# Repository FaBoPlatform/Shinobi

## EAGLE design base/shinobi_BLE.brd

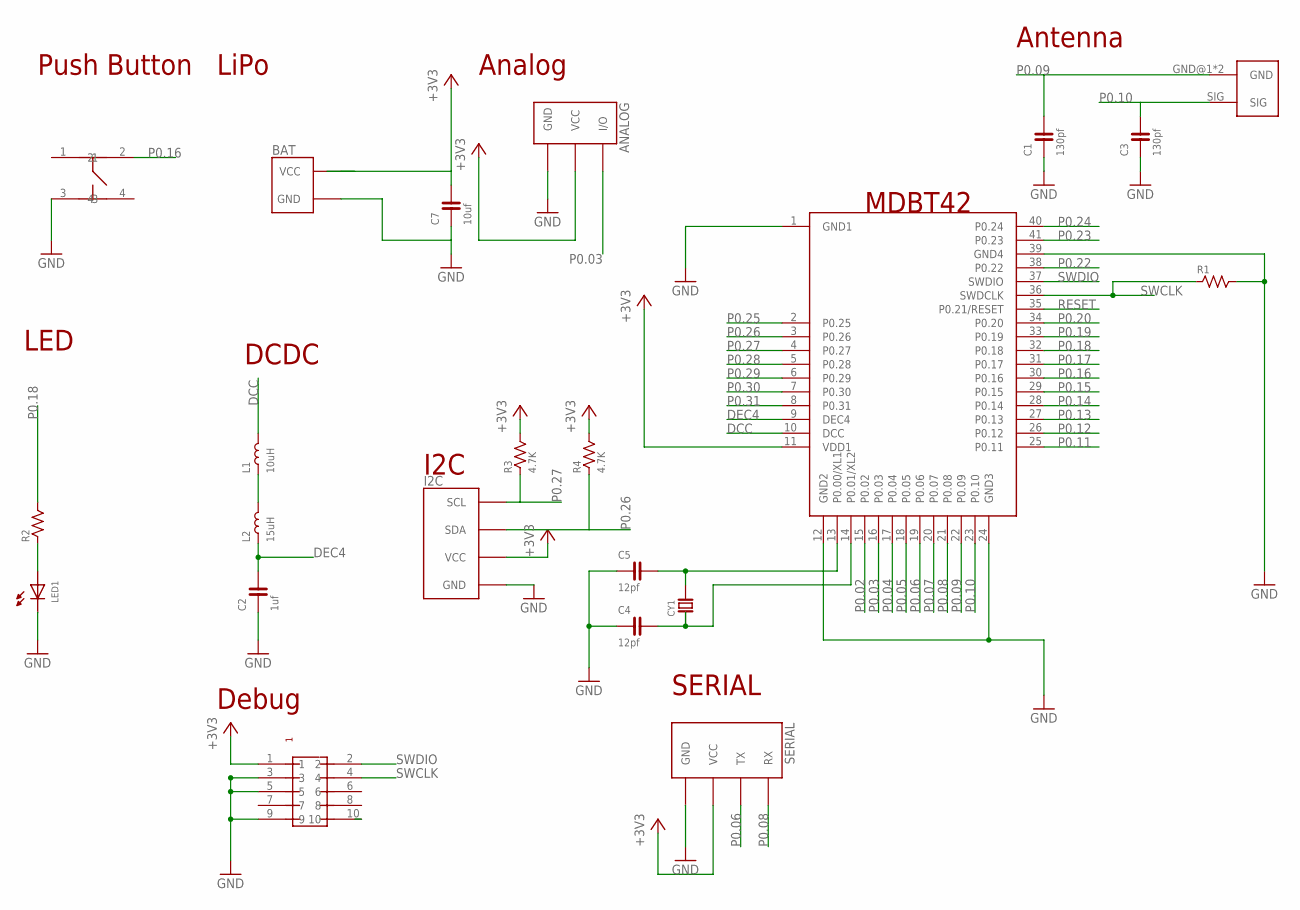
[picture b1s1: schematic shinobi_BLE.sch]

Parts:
ANALOG: FABO_BRICK_3PIN-S03B-PASK-2_LONG; FABO_BRICK_3PIN_S03B-PASK-2_LONG
BAT: FABO_BRICK_2PIN_SIDE; FABO_BRICK_2PIN_S02B−PASK-2_SILK
C1, C3: 130pf; 0603
C2: 1uf; 0603
C4, C5: 12pf; 0603
C7: 10uf; 0603
CY1: CRYSTAL-ABS07; ABRACON-ABS07-32.768KHZ
I2C: FABO_BRICK_I2C-S04B-PASK-2_LONG; FABO_BRICK_I2C_S04B-PASK-2_LONG
L1: 10uH; 0603
L2: 15uH; 1812
LED1: LED-0603; 0603
R1, R2: RESISTOR-0603; 0603
R3, R4: 4.7K; 0603
SERIAL: FABO_BRICK_SERIAL-S04B-PASK-2_LONG; FABO_BRICK_SERIAL_S04B-PASK-2_LONG
U$2: RAYTAC-MDBT42
U$4: PIN-HEADER-SMT(1.27MM)2X5
U$5: SWICTH-4P(KMR2); SWITCH-4P(KMR2)
UF1: HIROSE-U.FL; HIROSE-UF.L

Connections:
+3V3: ANALOG.VCC, BAT.VCC, C7.2, I2C.VCC, R3.2, R4.2, SERIAL.VCC, U$2.11 (VDD1), U$4.1
DCC: L1.2, U$2.10 (DCC)
DEC4: C2.2, L2.P$1 (1), U$2.9 (DEC4)
GND: ANALOG.GND, BAT.GND, C1.1, C2.1, C3.1, C4.1, C5.1, C7.1, I2C.GND, LED1.CATHODE, R1.2, SERIAL.GND, U$2.1 (GND1), U$2.12 (GND2), U$2.24 (GND3), U$2.39 (GND4), U$4.3, U$4.5, U$4.9, U$5.3
unnamed: LED1.ANODE, R2.1
unnamed: L1.1, L2.P$2 (2)
unnamed: C5.2, CY1.P$2, U$2.13 (P0.00/XL1)
unnamed: C4.2, CY1.P$1, U$2.14 (P0.01/XL2)
P0.02: U$2.15 (P0.02)
P0.03: ANALOG.I/O, U$2.16 (P0.03)
P0.04: U$2.17 (P0.04)
P0.05: U$2.18 (P0.05)
P0.06: SERIAL.TX, U$2.19 (P0.06)
P0.07: U$2.20 (P0.07)
P0.08: SERIAL.RX, U$2.21 (P0.08)
P0.09: C1.2, U$2.22 (P0.09), UF1.GND@1 (GND), UF1.GND@2 (GND)
P0.10: C3.2, U$2.23 (P0.10), UF1.SIG
P0.11: U$2.25 (P0.11)
P0.12: U$2.26 (P0.12)
P0.13: U$2.27 (P0.13)
P0.14: U$2.28 (P0.14)
P0.15: U$2.29 (P0.15)
P0.16: U$2.30 (P0.16), U$5.2
P0.17: U$2.31 (P0.17)
P0.18: R2.2, U$2.32 (P0.18)
P0.19: U$2.33 (P0.19)
P0.20: U$2.34 (P0.20)
P0.22: U$2.38 (P0.22)
P0.23: U$2.41 (P0.23)
P0.24: U$2.40 (P0.24)
P0.25: U$2.2 (P0.25)
P0.26: I2C.SDA, R4.1, U$2.3 (P0.26)
P0.27: I2C.SCL, R3.1, U$2.4 (P0.27)
P0.28: U$2.5 (P0.28)
P0.29: U$2.6 (P0.29)
P0.30: U$2.7 (P0.30)
P0.31: U$2.8 (P0.31)
RESET: U$2.35 (P0.21/RESET)
RESET1: U$4.10
SWCLK: R1.1, U$2.36 (SWDCLK), U$4.4
SWDIO: U$2.37 (SWDIO), U$4.2

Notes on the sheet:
Push Button
MDBT42
LED
Debug
DCDC
Analog
I2C
SERIAL
LiPo
Antenna

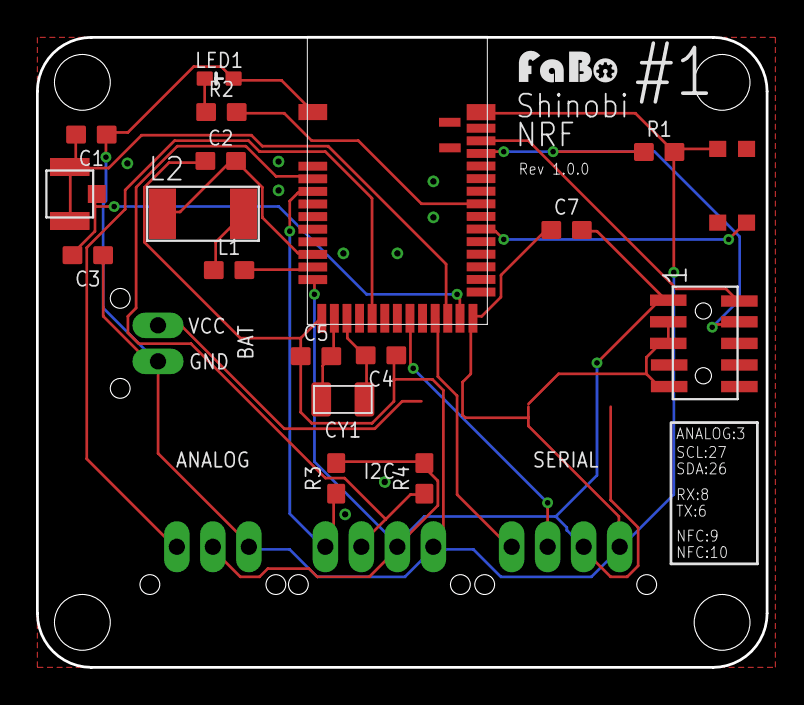
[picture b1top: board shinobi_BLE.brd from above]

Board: 2 copper layers, 40.5 x 35.0 mm, 24 parts (0 on the bottom side), 19 nets.

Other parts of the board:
U$1: FABO-SHINOBI
U$3: LOGO_FABO_S

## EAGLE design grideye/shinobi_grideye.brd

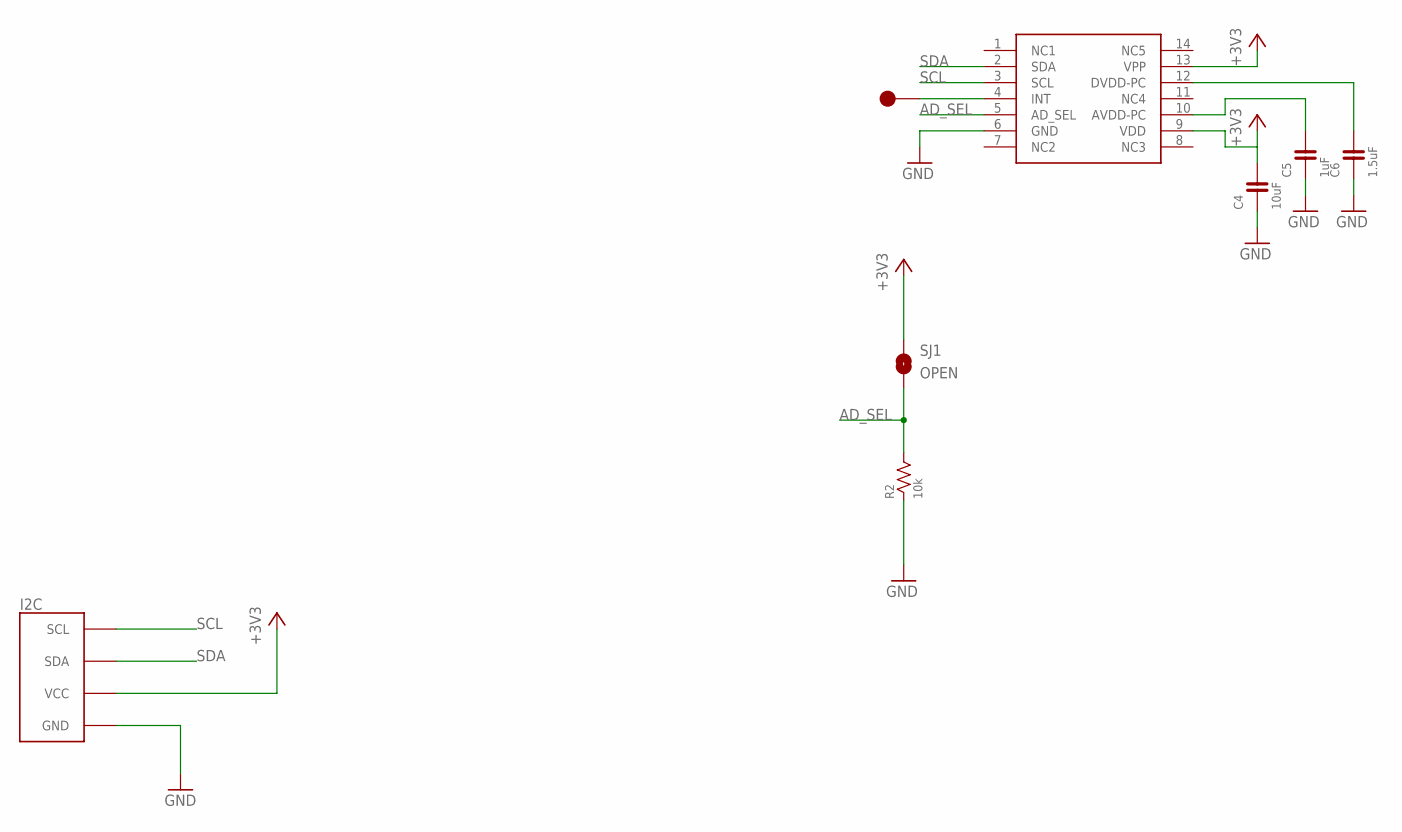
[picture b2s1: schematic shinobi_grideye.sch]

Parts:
C4: 10uF; 0603
C5: 1uF; 0603
C6: 1.5uF; 0603
GRIDEYE: PN-AMG8331; PANASONIC-AMG8831
I2C: FABO_BRICK_I2C-S04B-PASK-2_LONG; FABO_BRICK_I2C_S04B-PASK-2_LONG
INT: INT; TP-15
R2: 10k; 0603
SJ1: OPEN; SMD-JUMPER-2-OPEN

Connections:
+3V3: C4.2, GRIDEYE.9 (VDD), GRIDEYE.13 (VPP), I2C.VCC, SJ1.1
AD_SEL: GRIDEYE.5 (AD_SEL), R2.2, SJ1.2
GND: C4.1, C5.1, C6.1, GRIDEYE.6 (GND), I2C.GND, R2.1
unnamed: GRIDEYE.4 (INT), INT.1
unnamed: C6.2, GRIDEYE.12 (DVDD-PC)
unnamed: C5.2, GRIDEYE.10 (AVDD-PC)
SCL: GRIDEYE.3 (SCL), I2C.SCL
SDA: GRIDEYE.2 (SDA), I2C.SDA

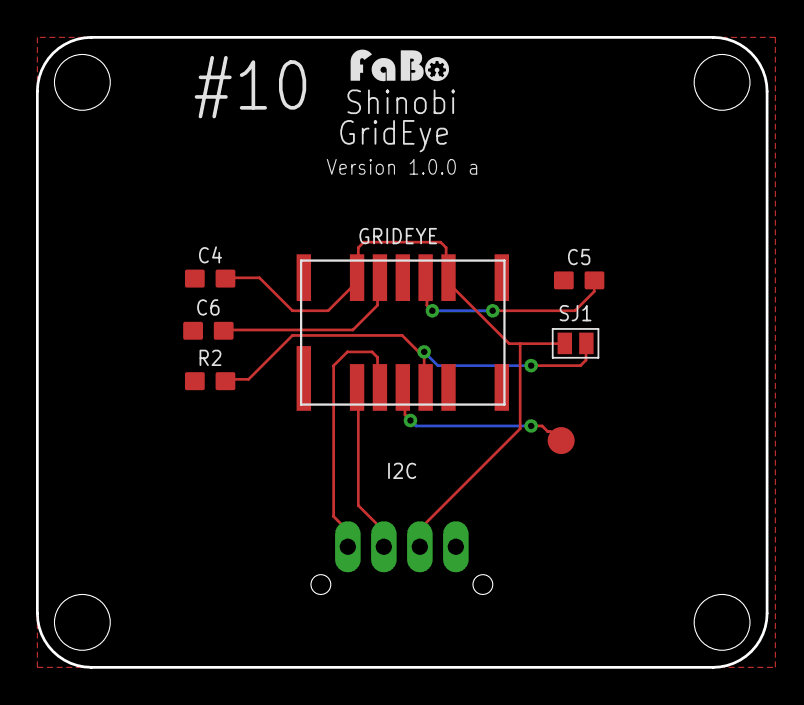
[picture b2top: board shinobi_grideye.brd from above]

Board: 2 copper layers, 40.5 x 35.0 mm, 10 parts (0 on the bottom side), 8 nets.

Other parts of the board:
U$2: LOGO_FABO_S
U$3: FABO-SHINOBI

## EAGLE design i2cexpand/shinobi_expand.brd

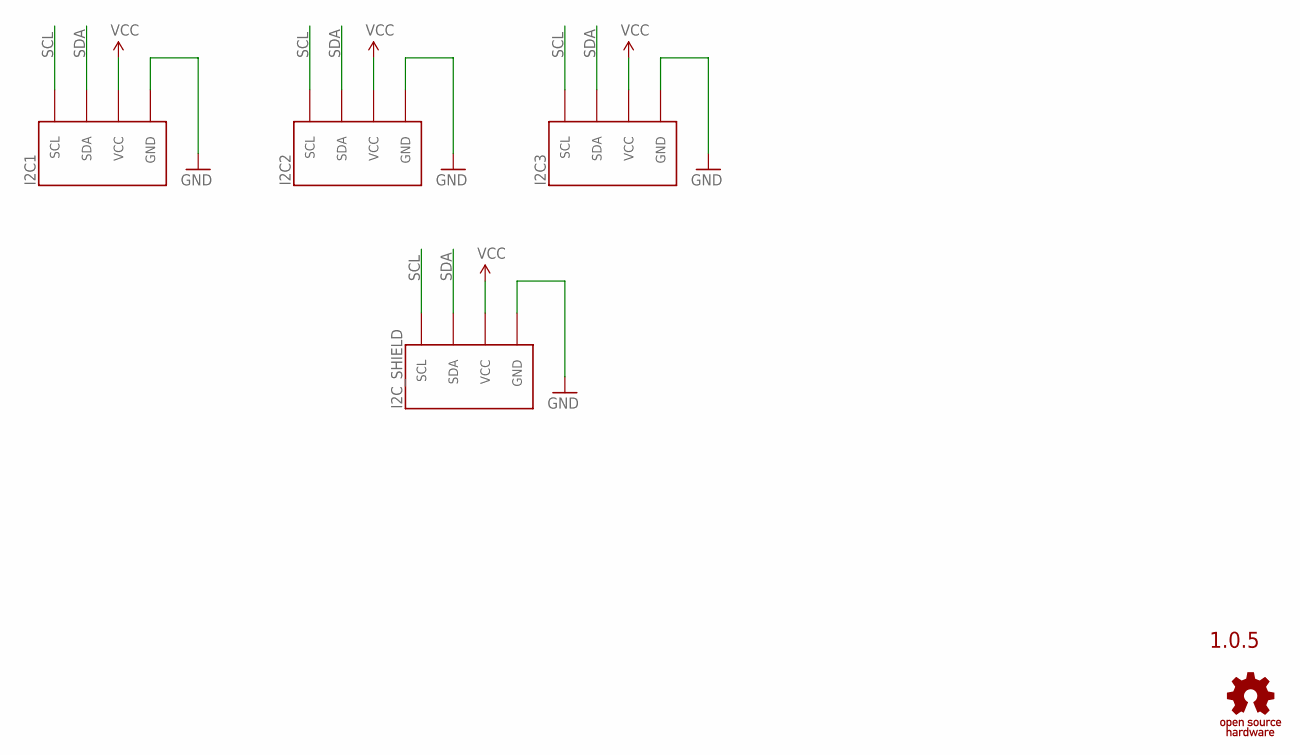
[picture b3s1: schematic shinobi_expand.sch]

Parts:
I2C1, I2C2, I2C3, I2C_SHIELD: FABO_BRICK_I2C-S04B-PASK-2_LONG; FABO_BRICK_I2C_S04B-PASK-2_LONG
U$11: LOGO_OSHW-M_BOTTOM; LOGO_OSHW_M_BOTTOM

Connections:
GND: I2C1.GND, I2C2.GND, I2C3.GND, I2C_SHIELD.GND
SCL: I2C1.SCL, I2C2.SCL, I2C3.SCL, I2C_SHIELD.SCL
SDA: I2C1.SDA, I2C2.SDA, I2C3.SDA, I2C_SHIELD.SDA
VCC: I2C1.VCC, I2C2.VCC, I2C3.VCC, I2C_SHIELD.VCC

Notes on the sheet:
1.0.5

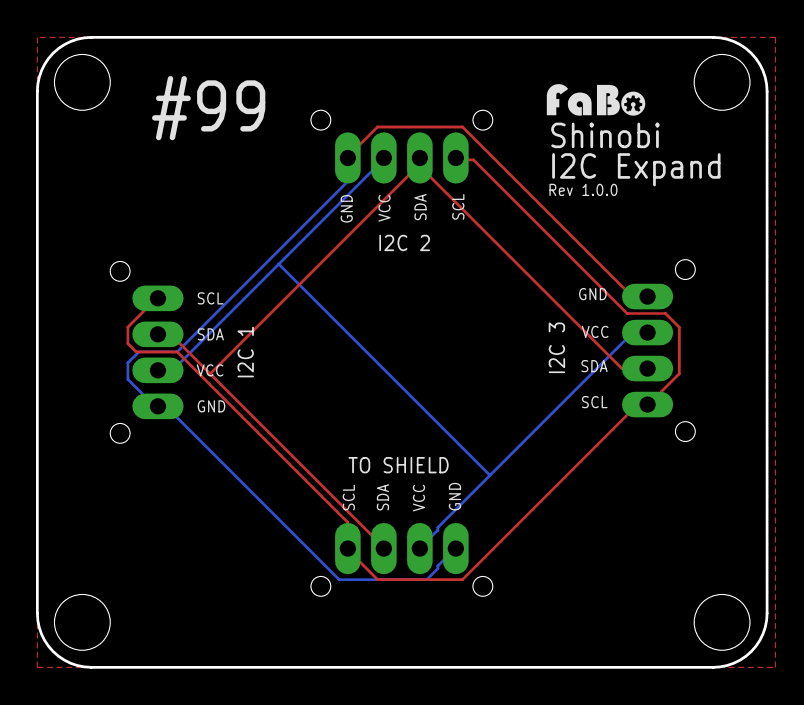
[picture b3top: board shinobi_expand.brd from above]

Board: 2 copper layers, 40.5 x 35.0 mm, 7 parts (0 on the bottom side), 4 nets.

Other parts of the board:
U$2: FABO-SHINOBI
U$3: LOGO_FABO_S

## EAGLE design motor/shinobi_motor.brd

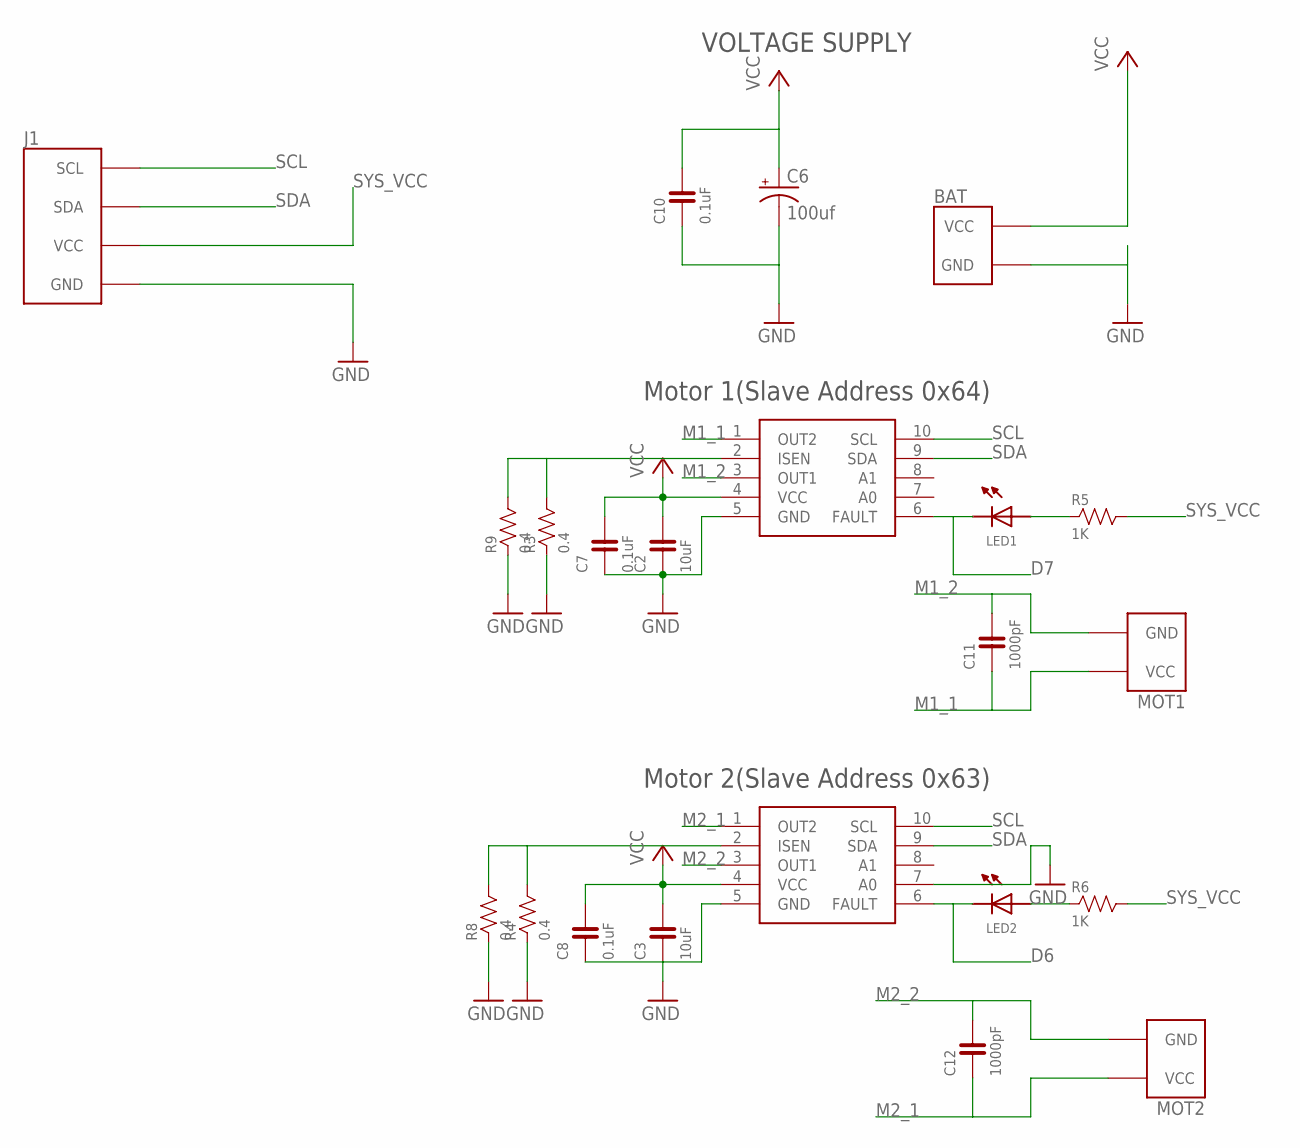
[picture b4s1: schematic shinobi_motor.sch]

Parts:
BAT: FABO_BRICK_2PIN_SIDE; FABO_BRICK_2PIN_S02B−PASK-2_SILK
C2, C3: 10uF; 0603
C6: 100uf; 153CLV-0405
C7, C8, C10: 0.1uF; 0603
C11, C12: 1000pF; 0603
J1: FABO_BRICK_I2C-S04B-PASK-2_LONG; FABO_BRICK_I2C_S04B-PASK-2_LONG
LED1, LED2: LED-0603; 0603
MOT1, MOT2: FABO_BRICK_2PIN_SIDE; FABO_BRICK_2PIN_S02B−PASK-2_SILK
R3, R4, R8, R9: 0.4; 0603
R5, R6: 1K; 0603
U$8, U$10: DRV8830

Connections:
D6: LED2.CATHODE, U$10.6 (FAULT)
D7: LED1.CATHODE, U$8.6 (FAULT)
GND: BAT.GND, C2.1, C3.1, C6.-, C7.1, C8.1, C10.1, J1.GND, R3.1, R4.1, R8.1, R9.1, U$8.5 (GND), U$10.5 (GND), U$10.7 (A0)
M1_1: C11.1, MOT1.VCC, U$8.1 (OUT2)
M1_2: C11.2, MOT1.GND, U$8.3 (OUT1)
M2_1: C12.1, MOT2.VCC, U$10.1 (OUT2)
M2_2: C12.2, MOT2.GND, U$10.3 (OUT1)
unnamed: R3.2, R9.2, U$8.2 (ISEN)
unnamed: R4.2, R8.2, U$10.2 (ISEN)
unnamed: LED1.ANODE, R5.1
unnamed: LED2.ANODE, R6.1
SCL: J1.SCL, U$8.10 (SCL), U$10.10 (SCL)
SDA: J1.SDA, U$8.9 (SDA), U$10.9 (SDA)
SYS_VCC: J1.VCC, R5.2, R6.2
VCC: BAT.VCC, C2.2, C3.2, C6.+, C7.2, C8.2, C10.2, U$8.4 (VCC), U$10.4 (VCC)

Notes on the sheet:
VOLTAGE SUPPLY
Motor 1(Slave Address 0x64)
Motor 2(Slave Address 0x63)

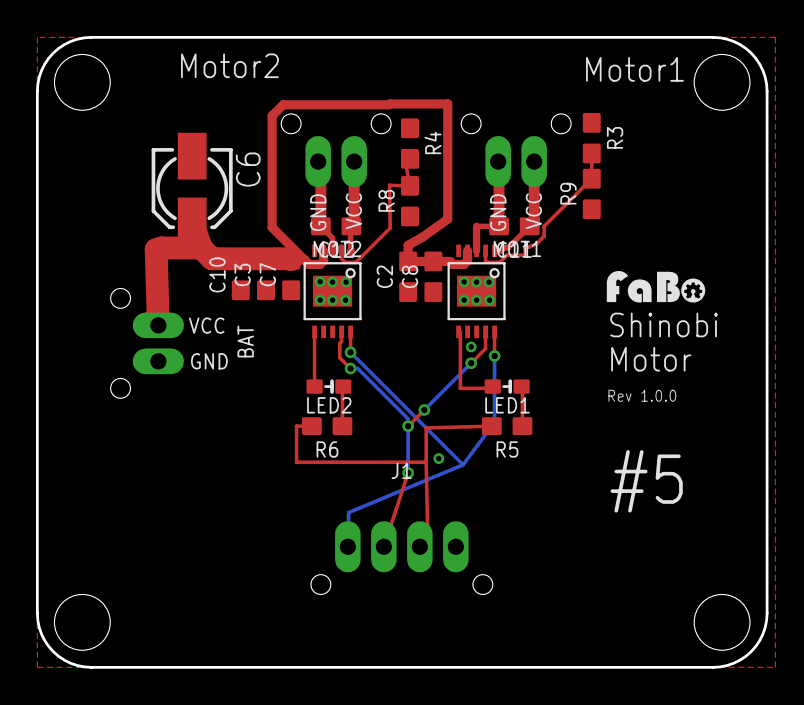
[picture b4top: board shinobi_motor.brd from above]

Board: 2 copper layers, 40.5 x 35.0 mm, 24 parts (0 on the bottom side), 15 nets.

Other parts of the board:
U$1: FABO-SHINOBI
U$2: LOGO_FABO_S

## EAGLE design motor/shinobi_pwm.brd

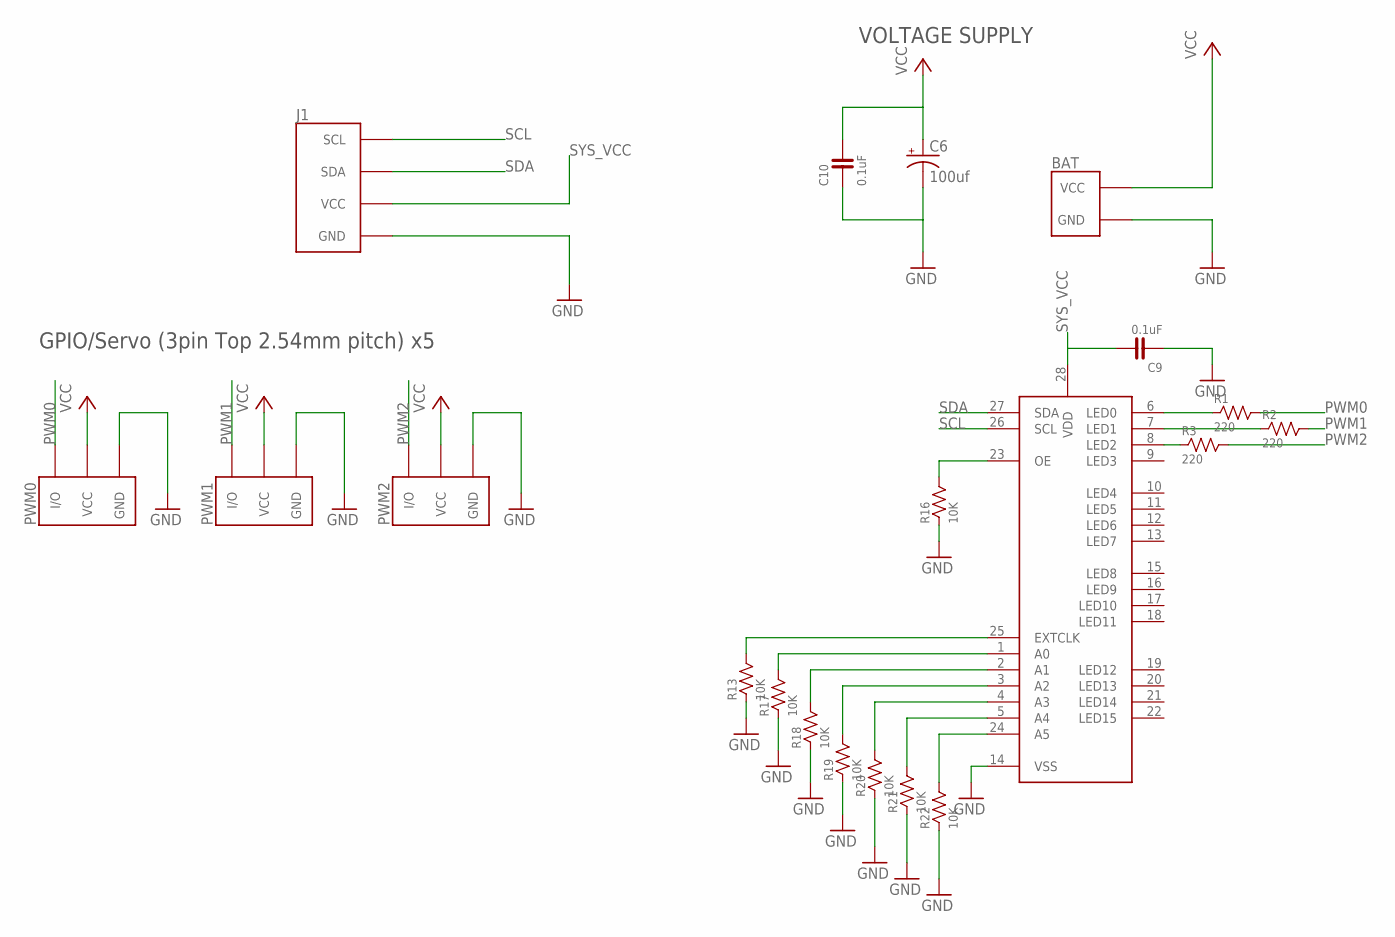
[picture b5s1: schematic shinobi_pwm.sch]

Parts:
BAT: FABO_BRICK_2PIN_SIDE; FABO_BRICK_2PIN_S02B−PASK-2_SILK
C6: 100uf; 153CLV-0405
C9, C10: 0.1uF; 0603
J1: FABO_BRICK_I2C-S04B-PASK-2_LONG; FABO_BRICK_I2C_S04B-PASK-2_LONG
PWM0, PWM1, PWM2: FABO_BRICK_3PIN-HEADER; FABO_BRICK_3PIN_HEADER
R1, R2, R3: 220; 0603
R13, R22: 10K; 0402
R16, R17, R18, R19, R20, R21: 10K; 0603
U$9: PCA9685

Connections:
GND: BAT.GND, C6.-, C9.1, C10.1, J1.GND, PWM0.GND, PWM1.GND, PWM2.GND, R13.P$1 (1), R16.1, R17.1, R18.1, R19.1, R20.1, R21.1, R22.P$1 (1), U$9.14 (VSS)
LED0: R1.1, U$9.6 (LED0)
LED1: R2.1, U$9.7 (LED1)
LED2: R3.1, U$9.8 (LED2)
unnamed: R16.2, U$9.23 (OE)
unnamed: R13.P$2 (2), U$9.25 (EXTCLK)
unnamed: R17.2, U$9.1 (A0)
unnamed: R18.2, U$9.2 (A1)
unnamed: R19.2, U$9.3 (A2)
unnamed: R20.2, U$9.4 (A3)
unnamed: R21.2, U$9.5 (A4)
unnamed: R22.P$2 (2), U$9.24 (A5)
PWM0: PWM0.I/O, R1.2
PWM1: PWM1.I/O, R2.2
PWM2: PWM2.I/O, R3.2
SCL: J1.SCL, U$9.26 (SCL)
SDA: J1.SDA, U$9.27 (SDA)
SYS_VCC: C9.2, J1.VCC, U$9.28 (VDD)
VCC: BAT.VCC, C6.+, C10.2, PWM0.VCC, PWM1.VCC, PWM2.VCC

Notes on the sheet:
VOLTAGE SUPPLY
GPIO/Servo (3pin Top 2.54mm pitch) x5

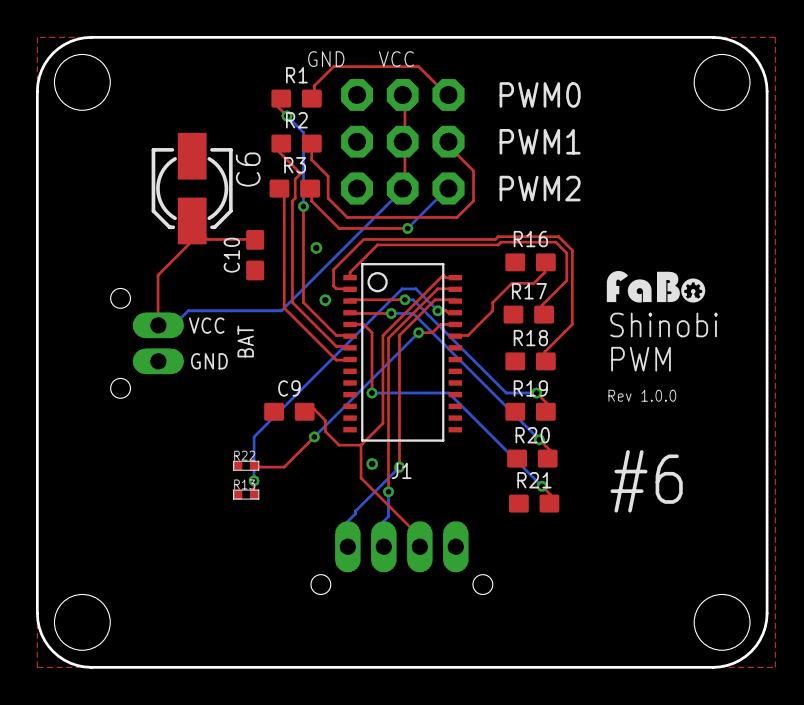
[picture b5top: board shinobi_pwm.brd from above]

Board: 2 copper layers, 40.5 x 35.0 mm, 22 parts (0 on the bottom side), 19 nets.

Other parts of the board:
U$1: FABO-SHINOBI
U$2: LOGO_FABO_S

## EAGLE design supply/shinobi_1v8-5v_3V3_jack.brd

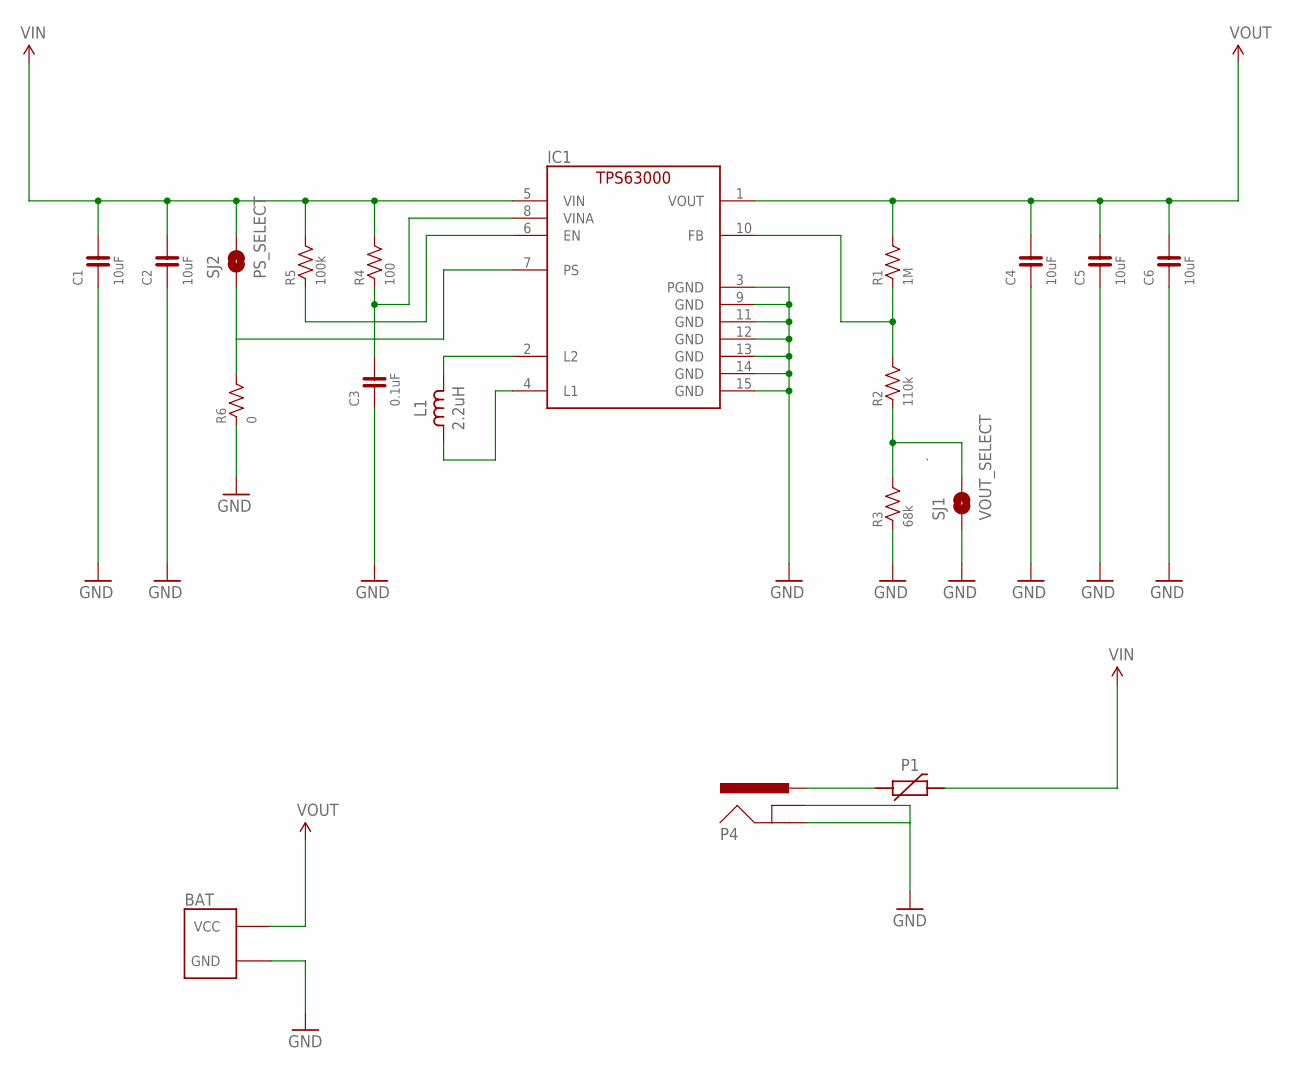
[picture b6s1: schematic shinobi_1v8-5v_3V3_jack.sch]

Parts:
BAT: FABO_BRICK_2PIN_SIDE; FABO_BRICK_2PIN_S02B−PASK-2_SILK
C1, C2, C4, C5, C6: 10uF; 0603-NARROW
C3: 0.1uF; 0603-NARROW
IC1: TPS63000DRC; VSON-10
L1: 2.2uH; LQH3NPN
P1: POLYSWITCH1210; 1210
P4: DC-JACKMA04339A0; M04339A0
R1: 1M; 0603-NARROW
R2: 110k; 0603-NARROW
R3: 68k; 0603-NARROW
R4: 100; 0603-NARROW
R5: 100k; 0603-NARROW
R6: 0; 0603-NARROW
SJ1: VOUT_SELECT; SMD-JUMPER-2-SHORT
SJ2: PS_SELECT; SMD-JUMPER-2-SHORT

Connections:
EN: IC1.6 (EN), R5.1
FB: IC1.10 (FB), R1.1, R2.2
GND: BAT.GND, C1.1, C2.1, C3.1, C4.1, C5.1, C6.1, IC1.3 (PGND), IC1.9 (GND), IC1.11 (GND), IC1.12 (GND), IC1.13 (GND), IC1.14 (GND), IC1.15 (GND), P4.GND@2 (GND), P4.GND@3 (GNDBREAK), R3.1, R6.1, SJ1.2
L1: IC1.4 (L1), L1.1
L2: IC1.2 (L2), L1.2
unnamed: R2.1, R3.2, SJ1.1
unnamed: P1.P$1 (1), P4.VCC (PWR)
PS: IC1.7 (PS), R6.2, SJ2.2
VIN: C1.2, C2.2, IC1.5 (VIN), P1.P$2 (2), R4.2, R5.2, SJ2.1
VINA: C3.2, IC1.8 (VINA), R4.1
VOUT: BAT.VCC, C4.2, C5.2, C6.2, IC1.1 (VOUT), R1.2

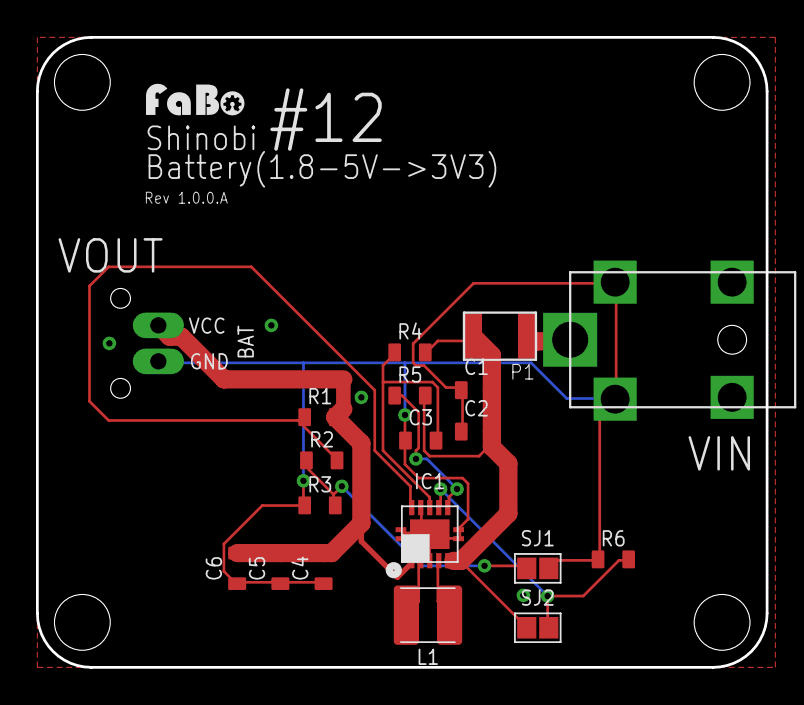
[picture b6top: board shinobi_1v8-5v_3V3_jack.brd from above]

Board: 2 copper layers, 40.5 x 35.0 mm, 21 parts (0 on the bottom side), 11 nets.

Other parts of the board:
U$2: LOGO_FABO_S
U$3: FABO-SHINOBI

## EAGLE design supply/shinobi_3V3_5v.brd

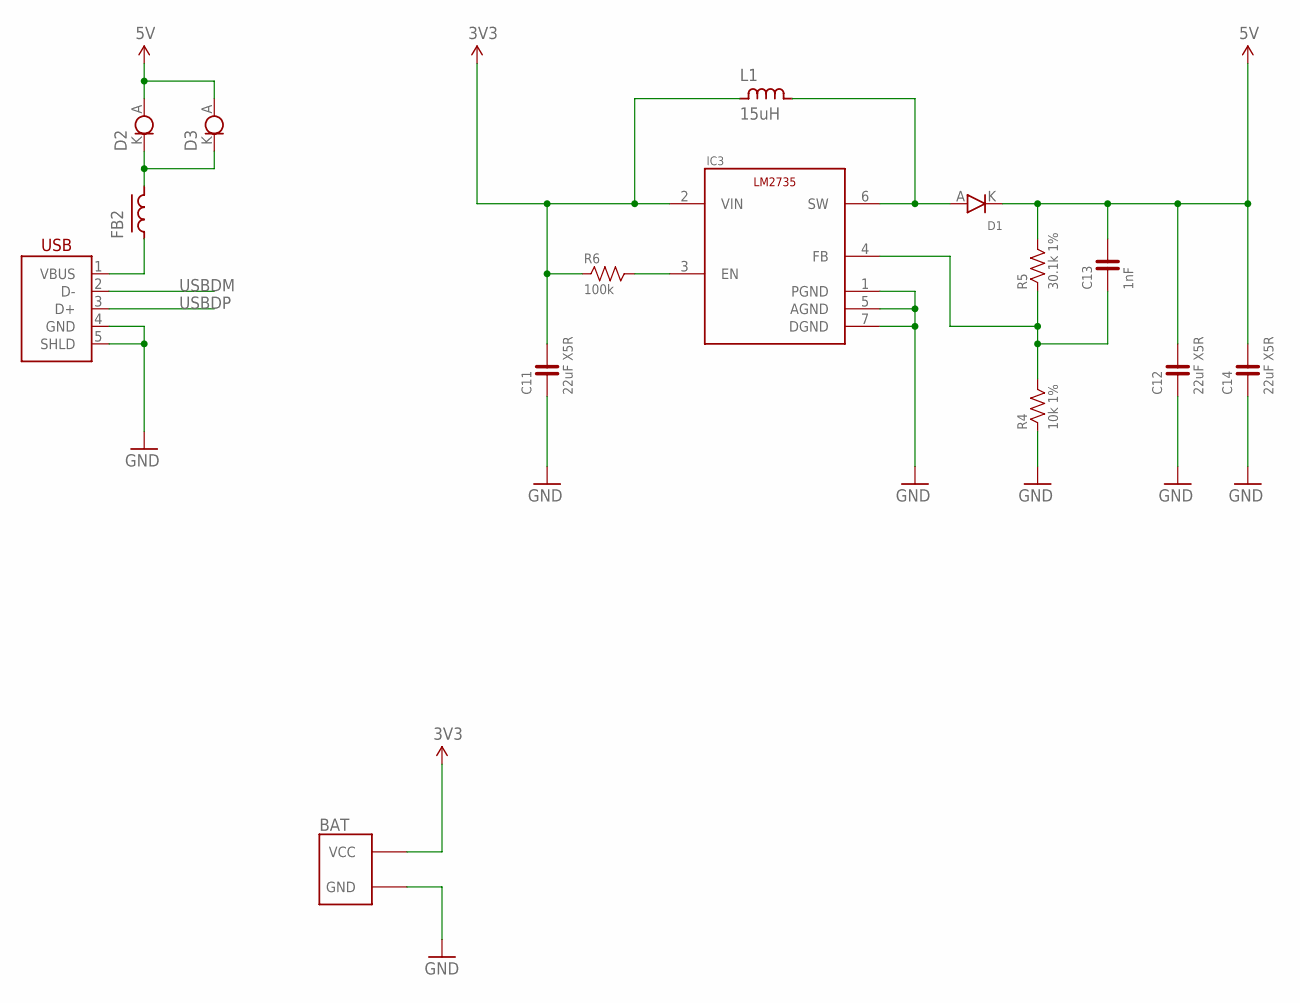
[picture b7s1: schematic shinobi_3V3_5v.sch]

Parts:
BAT: FABO_BRICK_2PIN_SIDE; FABO_BRICK_2PIN_S02B−PASK-2_SILK
C11, C12, C14: 22uF X5R; 0603-NARROW
C13: 1nF; 0603-NARROW
D1: 20V1A; ST-MITE-FLAT
D2, D3: CRD_S-153T; CRD-S-153T
FB2: FERRITEBEADS; EIA0603
IC3: LM2735YQSDX; WSON-6
L1: 15uH; NR6028
R4: 10k 1%; 0603-NARROW
R5: 30.1k 1%; 0603-NARROW
R6: 100k; 0603-NARROW
USB1: USB-CONN_SMT; SM05B-PASS

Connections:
3V3: BAT.VCC, C11.2, IC3.2 (VIN), L1.1, R6.1
5V: C12.2, C13.2, C14.2, D1.K, D2.A, D3.A, R5.2
DCDCEN: IC3.3 (EN), R6.2
FB: C13.1, IC3.4 (FB), R4.2, R5.1
GND: BAT.GND, C11.1, C12.1, C14.1, IC3.1 (PGND), IC3.5 (AGND), IC3.7 (DGND), R4.1, USB1.4 (GND), USB1.5 (SHLD)
unnamed: D2.K, D3.K, FB2.2
SW: D1.A, IC3.6 (SW), L1.2
USBDM: USB1.2 (D-)
USBDP: USB1.3 (D+)
USBVBUS: FB2.1, USB1.1 (VBUS)

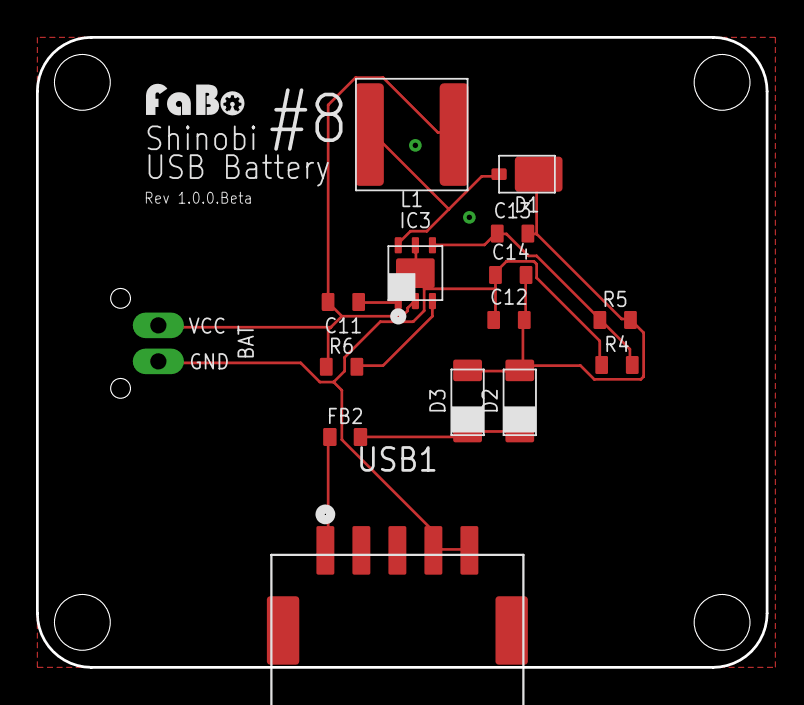
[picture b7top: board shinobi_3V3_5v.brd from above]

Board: 2 copper layers, 40.5 x 35.0 mm, 17 parts (0 on the bottom side), 8 nets.

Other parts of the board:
U$2: LOGO_FABO_S
U$3: FABO-SHINOBI

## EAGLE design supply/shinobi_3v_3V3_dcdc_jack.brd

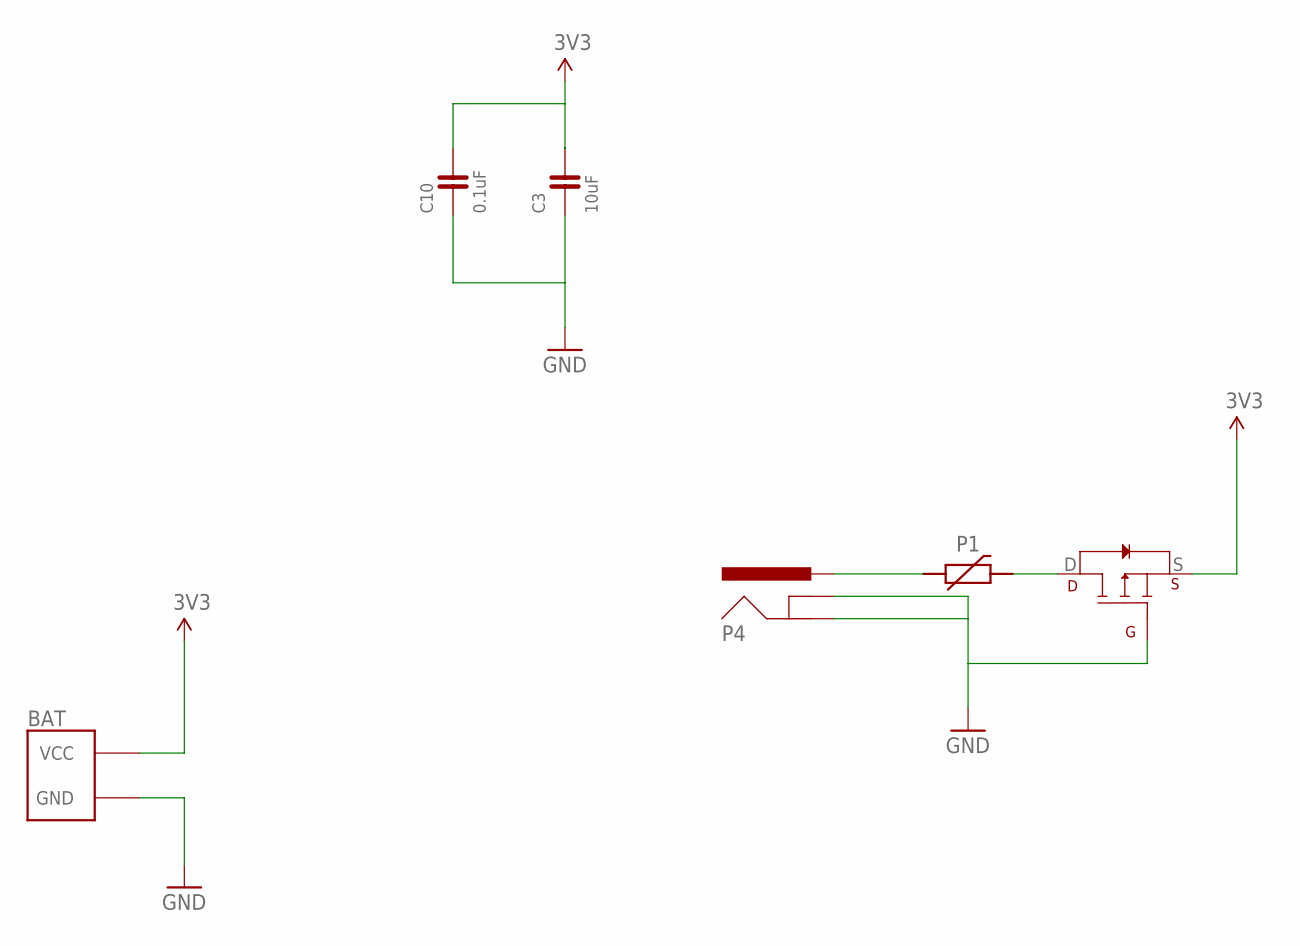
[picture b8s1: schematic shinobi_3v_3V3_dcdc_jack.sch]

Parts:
BAT: FABO_BRICK_2PIN_SIDE; FABO_BRICK_2PIN_S02B−PASK-2_SILK
C3: 10uF; 0603
C10: 0.1uF; 0603
M1: AOD417
P1: POLYSWITCH1210; 1210
P4: DC-JACKMA04339A0; M04339A0

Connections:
3V3: BAT.VCC, C3.2, C10.2, M1.S
GND: BAT.GND, C3.1, C10.1, M1.G, P4.GND@2 (GND), P4.GND@3 (GNDBREAK)
unnamed: P1.P$1 (1), P4.VCC (PWR)
unnamed: M1.D, P1.P$2 (2)

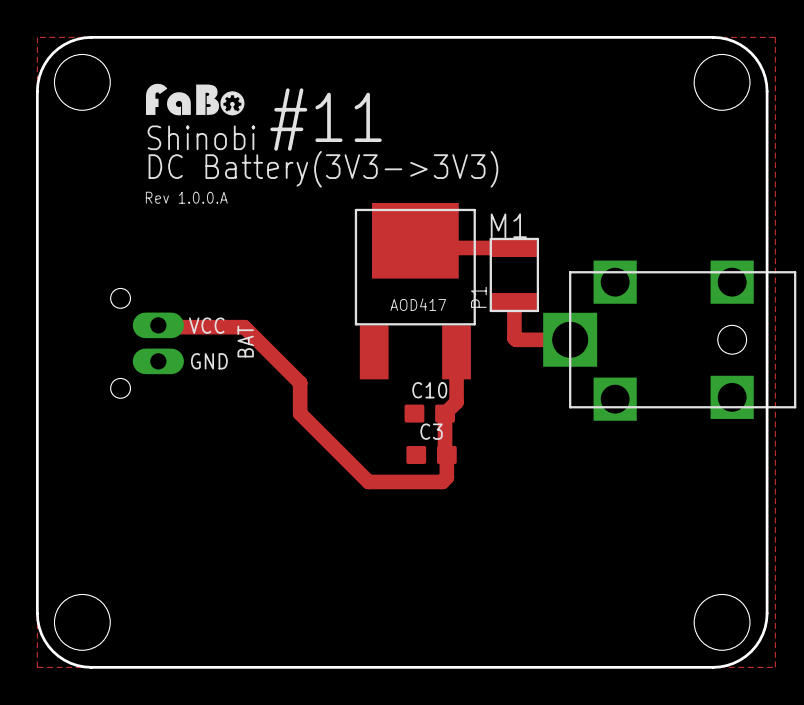
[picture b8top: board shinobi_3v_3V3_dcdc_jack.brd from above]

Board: 2 copper layers, 40.5 x 35.0 mm, 8 parts (0 on the bottom side), 4 nets.

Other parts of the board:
U$2: LOGO_FABO_S
U$3: FABO-SHINOBI

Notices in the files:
parts and their libraries:
FaBo-Inductor: Released under the Creative Commons Attribution-ShareAlike 4.0 License
https://creativecommons.org/licenses/by-sa/4.0
gclue: Released under the Creative Commons
SparkFun: Licensing: CC v3.0 Share-Alike You are welcome to use this library for commercial purposes.
